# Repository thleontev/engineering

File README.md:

# Engineering

Репозиторий инженерных проектов и разработок.

Здесь собраны законченные и демонстрационные проекты по электронике, встроенному ПО, CAD, прототипированию и подготовке изделий к производству.

## Проекты

### Fire Lamp

Настольный ночник с эффектом пламени и светомузыкой на базе ESP32-S3 и WLED.

В проекте объединены:

- механическая конструкция и CAD;
- проектирование схемы и печатной платы;
- силовая часть для адресной LED-матрицы;
- встроенное ПО и пользовательский модуль WLED;
- датчик движения и датчик освещённости;
- сборка, прототипирование и испытания.

→ [Fire Lamp](fire-lamp/)

### Подсолнух / Sunflower

Настольный ночник в форме подсолнуха со сменной лампой GX53.

В проекте объединены:

- предметный дизайн и механическая компоновка;
- справочная сборка STEP;
- детали для FDM-печати и проект Bambu Studio;
- перечень компонентов и крепежа;
- вариант лампы YNDX-00556 с управлением через Алису;
- визуализация внешнего вида и внутреннего устройства.

→ [Подсолнух](sunflower/)

## Принцип публикации

В репозитории размещаются только материалы, которые подходят для публичного просмотра и воспроизведения проекта. Рабочие внутренние документы, данные поставщиков, учётные данные и незавершённые эксперименты не публикуются.

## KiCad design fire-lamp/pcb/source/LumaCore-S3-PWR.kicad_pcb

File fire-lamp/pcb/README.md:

# PCB — LumaCore-S3-PWR

Электроника Fire Lamp построена на контроллере LumaCore-S3-PWR.

## Рендеры платы

### Верхняя сторона

### Нижняя сторона

## Исходники

В каталоге `source/` находятся исходники KiCad:

- проект;
- принципиальная схема;
- печатная плата.

Используемые проектом символы, посадочные места и модели компонентов находятся в `source/lib/`. Таблицы `sym-lib-table` и `fp-lib-table` используют относительные пути. Для открытия проекта установите KiCad 10 со стандартными библиотеками и откройте `source/LumaCore-S3-PWR.kicad_pro`.

В каталоге `production/` размещены открытые производственные данные, которые можно использовать для анализа платы и подготовки сборки.

## Проверки опубликованного набора

Исходники, BOM, координаты и рендеры обновлены 4 ноября 2026 года. ERC и DRC выполнены повторно именно для опубликованной структуры каталогов в KiCad 10.0.8:

- ERC: 0 ошибок и предупреждений;
- DRC с перезаливкой зон и проверкой соответствия схеме: 0 нарушений, 0 неподключённых элементов, 0 расхождений;
- C4 и C14 указаны отдельными строками BOM; C14 100 мкФ присутствует в координатах установки.

Отчёты сохранены в `production/`. Эти проверки и подтверждение работы прототипа не являются квалификацией серийного производства, испытанием на 8 А или подтверждением тепловых пределов.

## Основные параметры

- MCU: ESP32-S3-WROOM-1;
- питание изделия: 5 В;
- нагрузка: WS2812B 16×16;
- LED DATA: отдельный буферизированный цифровой выход;
- управление питанием LED;
- отдельное питание логики 3,3 В.

## Ревизия

Опубликованный набор PCB основан на LumaCore-S3-PWR R2.1.

Плата является частью проекта Fire Lamp, но может использоваться и как самостоятельная аппаратная платформа.

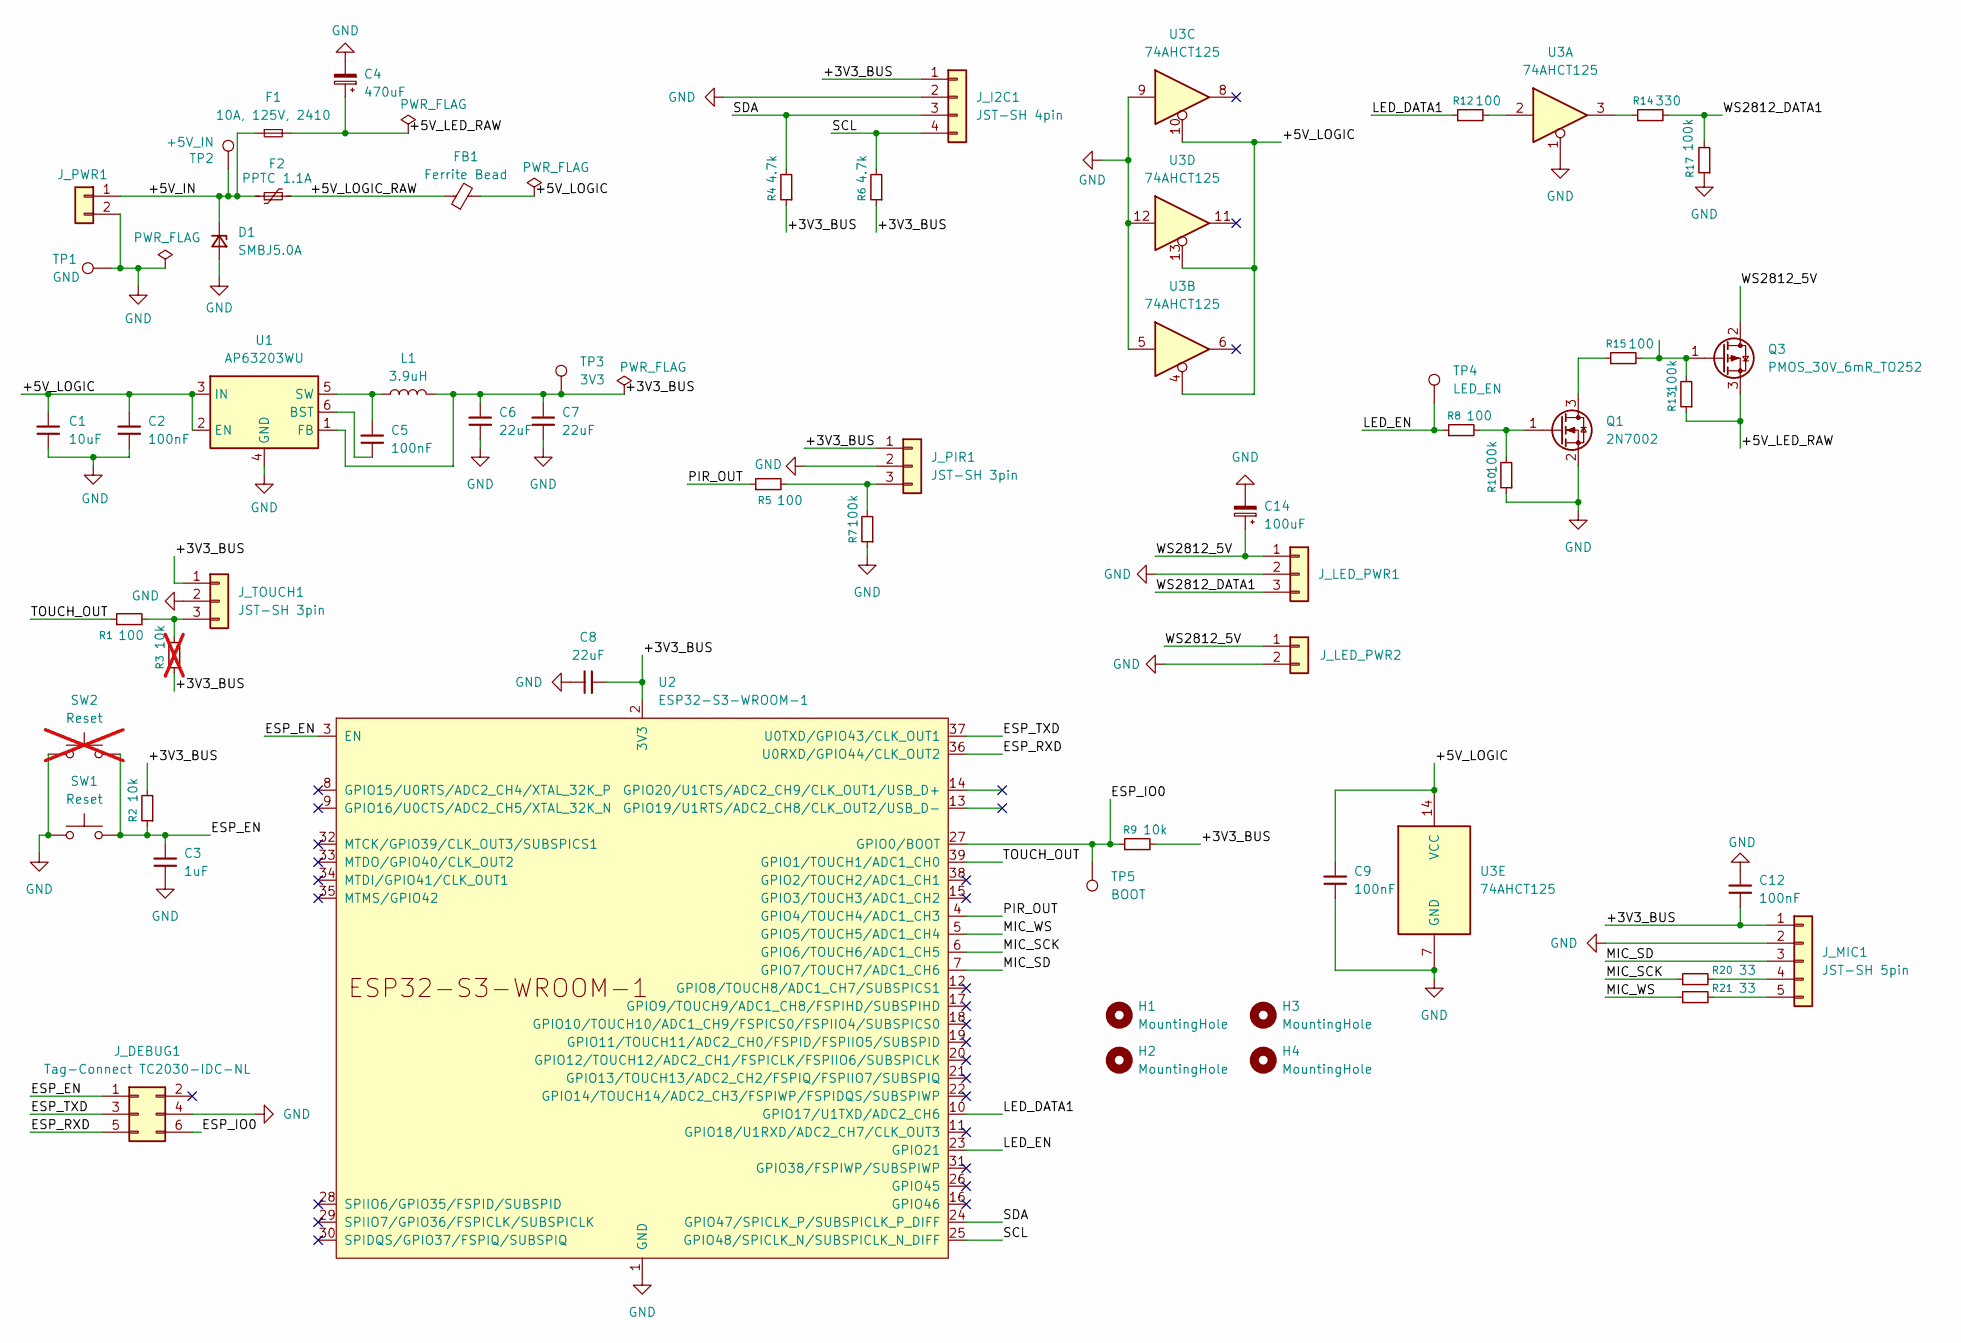
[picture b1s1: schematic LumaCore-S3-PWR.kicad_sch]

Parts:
C1: 10uF; C_1206_3216Metric
C2, C5, C9, C12: 100nF; C_0805_2012Metric
C3: 1uF; C_0805_2012Metric
C4: 470uF; CP_Elec_6.3x7.7; MPN EEEFTA471XAP
C6, C7, C8: 22uF; C_1206_3216Metric
C14: 100uF; CP_Elec_5x5.8; MPN EEE-FT1C101AR
D1: SMBJ5.0A; D_SMB; MPN SMBJ5.0A
F1: 10A, 125V, 2410; Fuse_Littelfuse_NANO2_452_2410; MPN 0451010.MRL
F2: PPTC 1.1A; Fuse_Polyfuse_Bourns_MF-MSMF110-16-2_1812; MPN MF-MSMF110/16-2
FB1: Ferrite Bead; L_0805_2012Metric; MPN BLM21PG121SN1D
H1, H2, H3, H4: MountingHole; MountingHole_2.2mm_M2
J_DEBUG1: Tag-Connect TC2030-IDC-NL; Tag-Connect_TC2030-IDC-NL_2x03_P1.27mm_Vertical
J_I2C1: JST-SH 4pin; JST_SH_BM04B-SRSS-TB_1x04-1MP_P1.00mm_Vertical
J_LED_PWR1: SolderCable_1x03_AWG16_DATA_P4.50_D2.00
J_LED_PWR2: SolderCable_1x02_AWG16_P4.50_D2.00
J_MIC1: JST-SH 5pin; JST_SH_BM05B-SRSS-TB_1x05-1MP_P1.00mm_Vertical
J_PIR1: JST-SH 3pin; JST_SH_BM03B-SRSS-TB_1x03-1MP_P1.00mm_Vertical
J_PWR1: SolderCable_1x02_AWG16_P4.50_D2.00
J_TOUCH1: JST-SH 3pin; JST_SH_BM03B-SRSS-TB_1x03-1MP_P1.00mm_Vertical
L1: 3.9uH; L_4020_4030_Universal_LumaCore; MPN MNR4030T3R9MT
Q1: 2N7002; SOT-23; MPN 2N7002
Q3: PMOS_30V_6mR_TO252; TO-252-3_TabPin2; MPN G050P03K
R1, R5, R8, R12, R15: 100; R_0805_2012Metric
R2, R9: 10k; R_0805_2012Metric
R3: 10k; R_0805_2012Metric; not fitted
R4, R6: 4.7k; R_0805_2012Metric
R7, R10, R13, R17: 100k; R_0805_2012Metric
R14: 330; R_0805_2012Metric
R20, R21: 33; R_0805_2012Metric
SW1: Reset; SW_SPST_B3U-1000P; MPN B3U-1000P
SW2: Reset; SW_SPST_B3U-1000P; MPN B3U-1000P; not fitted
TP1: GND; TestPoint_Pad_D1.0mm
TP2: +5V_IN; TestPoint_Pad_D1.0mm
TP3: 3V3; TestPoint_Pad_D1.0mm
TP4: LED_EN; TestPoint_Pad_D1.0mm
TP5: BOOT; TestPoint_Pad_D1.0mm
U1: AP63203WU; TSOT-23-6; MPN AP63203WU-7
U2: ESP32-S3-WROOM-1; MPN ESP32-S3-WROOM-1(16R8)
U3: 74AHCT125; SOIC-14_3.9x8.7mm_P1.27mm; MPN SN74AHCT125DR

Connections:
/+3V3_BUS: C6.1, C7.1, C8.1, C12.2, J_I2C1.1, J_MIC1.1, J_PIR1.1, J_TOUCH1.1, L1.2, R2.2, R3.1, R4.1, R6.1, R9.2, TP3.1 (1_1), U1.1 (FB), U2.2 (3V3)
/+5V_IN: D1.1 (K), F1.1, F2.1, J_PWR1.1, TP2.1 (1_1)
/+5V_LED_RAW: C4.1, F1.2, Q3.3 (S), R13.1
/+5V_LOGIC: C1.1, C2.1, C9.1, FB1.2, U1.2 (EN), U1.3 (IN), U3.4, U3.10, U3.13, U3.14 (VCC)
/+5V_LOGIC_RAW: F2.2, FB1.1
/ESP_EN: C3.1, J_DEBUG1.1, R2.1, SW1.2, SW2.2, U2.3 (EN)
/ESP_IO0: J_DEBUG1.6, R9.1, TP5.1 (1_1), U2.27 (GPIO0/BOOT)
/ESP_RXD: J_DEBUG1.5, U2.36 (U0RXD/GPIO44/CLK_OUT2)
/ESP_TXD: J_DEBUG1.3, U2.37 (U0TXD/GPIO43/CLK_OUT1)
/LED_DATA1: R12.1, U2.10 (GPIO17/U1TXD/ADC2_CH6)
/LED_EN: R8.1, TP4.1 (1_1), U2.23 (GPIO21)
/MIC_SCK: R20.1, U2.6 (GPIO6/TOUCH6/ADC1_CH5)
/MIC_SD: J_MIC1.3, U2.7 (GPIO7/TOUCH7/ADC1_CH6)
/MIC_WS: R21.1, U2.5 (GPIO5/TOUCH5/ADC1_CH4)
/PIR_OUT: R5.1, U2.4 (GPIO4/TOUCH4/ADC1_CH3)
/SCL: J_I2C1.4, R6.2, U2.25 (GPIO48/SPICLK_N/SUBSPICLK_N_DIFF)
/SDA: J_I2C1.3, R4.2, U2.24 (GPIO47/SPICLK_P/SUBSPICLK_P_DIFF)
/TOUCH_OUT: R1.1, U2.39 (GPIO1/TOUCH1/ADC1_CH0)
/WS2812_5V: C14.1, J_LED_PWR1.1, J_LED_PWR2.1, Q3.2 (D)
/WS2812_DATA1: J_LED_PWR1.3, R14.2, R17.2
GND: C1.2, C2.2, C3.2, C4.2, C6.2, C7.2, C8.2, C9.2, C12.1, C14.2, D1.2 (A), J_DEBUG1.4, J_I2C1.2, J_LED_PWR1.2, J_LED_PWR2.2, J_MIC1.2, J_PIR1.2, J_PWR1.2, J_TOUCH1.2, Q1.2 (S), R7.1, R10.1, R17.1, SW1.1, SW2.1, TP1.1 (1_1), U1.4 (GND), U2.1 (GND), U2.40 (GND), U2.41 (GND), U3.1, U3.5, U3.7 (GND), U3.9, U3.12
unnamed: J_MIC1.4, R20.2
unnamed: J_MIC1.5, R21.2
unnamed: J_PIR1.3, R5.2, R7.2
unnamed: J_TOUCH1.3, R1.2, R3.2
unnamed: Q1.3 (D), R15.1
unnamed: Q1.1 (G), R8.2, R10.2
unnamed: Q3.1 (G), R13.2, R15.2
unnamed: R12.2, U3.2
unnamed: R14.1, U3.3
unnamed: C5.2, U1.6 (BST)
unnamed: C5.1, L1.1, U1.5 (SW)

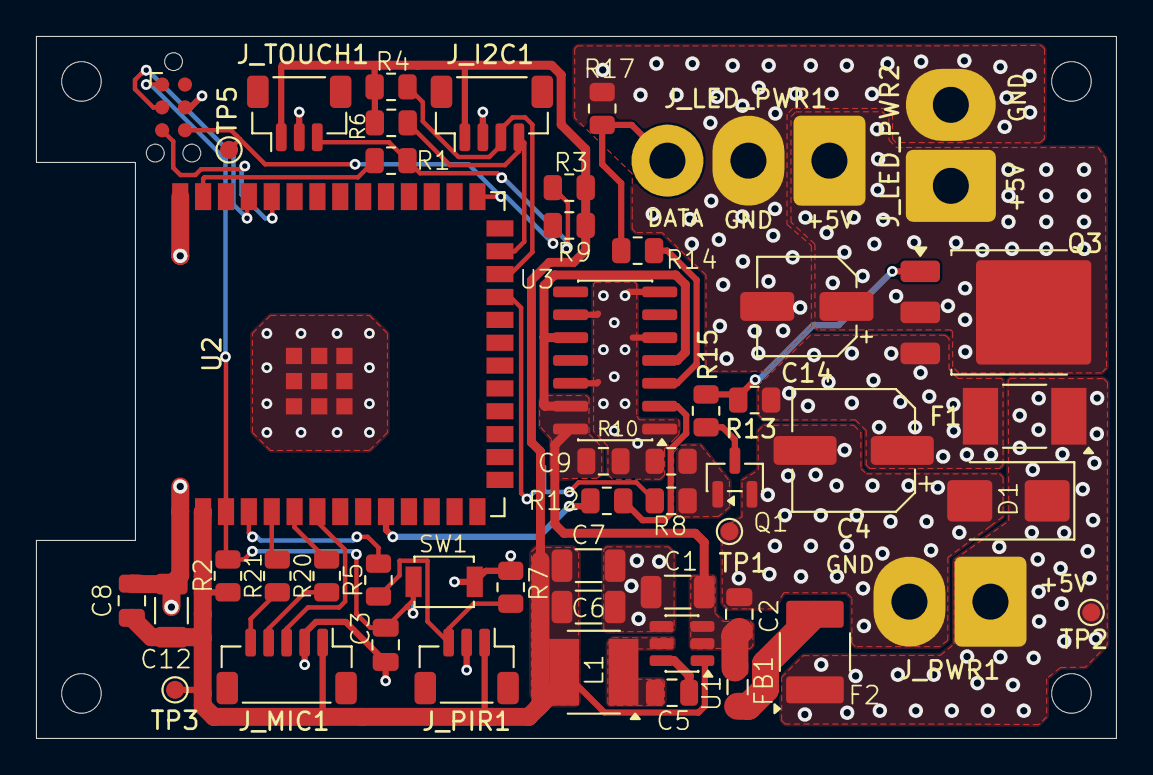
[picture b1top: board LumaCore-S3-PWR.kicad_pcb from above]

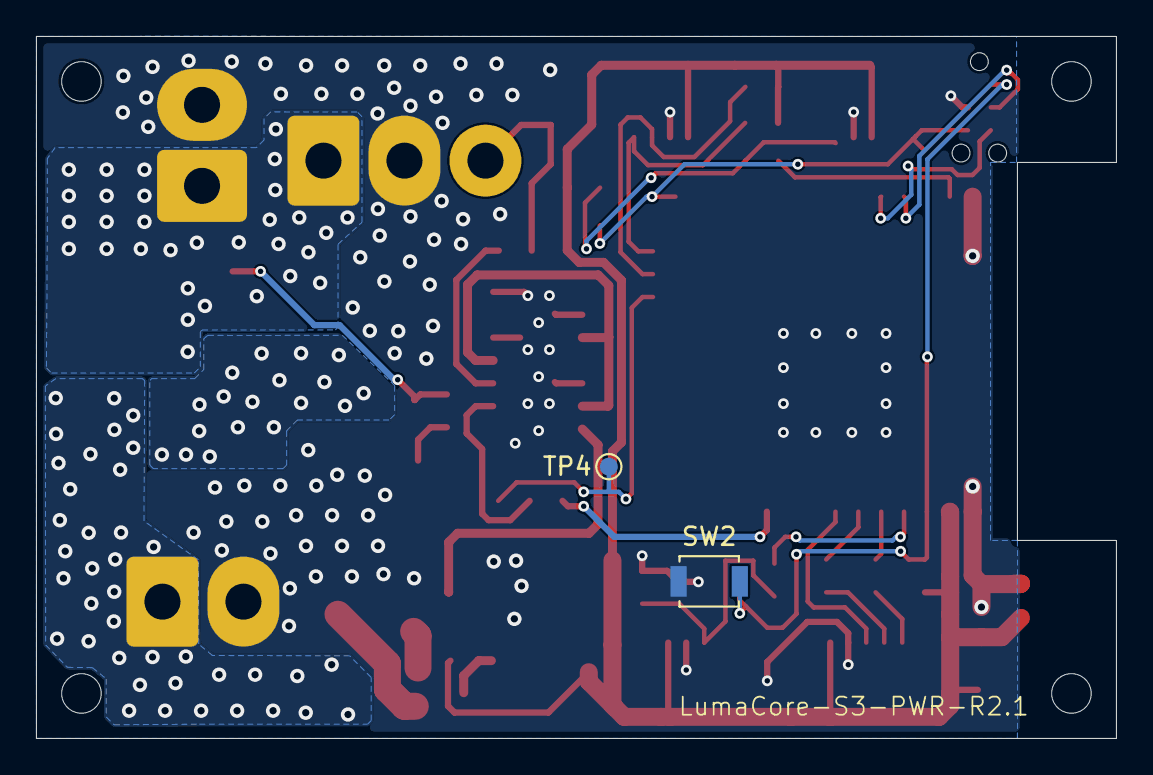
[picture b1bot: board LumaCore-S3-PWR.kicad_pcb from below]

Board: 2 copper layers, 60.0 x 39.0 mm, 57 parts (2 on the bottom side), 32 nets.

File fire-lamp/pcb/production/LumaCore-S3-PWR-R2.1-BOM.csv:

"Refs","Qty","Value","Footprint","Manufacturer","MPN","Supplier","Description","Specification"
"C1","1","10uF","Capacitor_SMD:C_1206_3216Metric","","","","Unpolarized capacitor, small symbol","10uF; 10V; X5R; ±10%; 1206"
"C2, C5, C9, C12","4","100nF","Capacitor_SMD:C_0805_2012Metric","","","","Unpolarized capacitor, small symbol","100nF; 50V; X7R; ±10%; 0805"
"C3","1","1uF","Capacitor_SMD:C_0805_2012Metric","","","","Unpolarized capacitor, small symbol","1uF; 16V; X7R; ±10%; 0805"
"C4","1","470uF","Capacitor_SMD:CP_Elec_6.3x7.7","","EEEFTA471XAP","","470uF 10V 105C SMD D6.3x7.7","470uF; 10V; 105°C; SMD 6.3x7.7mm"
"C6-C8","3","22uF","Capacitor_SMD:C_1206_3216Metric","","","","Unpolarized capacitor, small symbol","22uF; 10V; X7R; ±10%; 1206"
"C14","1","100uF","Capacitor_SMD:CP_Elec_5x5.8","","EEE-FT1C101AR","","100uF 16V 105C SMD 5x5.8","100uF; 16V; 105°C; SMD 5x5.8mm"
"D1","1","SMBJ5.0A","Diode_SMD:D_SMB","","SMBJ5.0A","","Unidirectional TVS diode, 600W, 5V, SMB / DO-214AA","TVS; SMBJ5.0A; 5.0V; 600W; SMB (DO-214AA)"
"F1","1","10A, 125V, 2410","LumaCore:Fuse_Littelfuse_NANO2_452_2410","","0451010.MRL","","10A, 125V, 2410","Fuse; 10A; 125V; 2410"
"F2","1","PPTC 1.1A","LumaCore:Fuse_Polyfuse_Bourns_MF-MSMF110-16-2_1812","","MF-MSMF110/16-2","","PPTC resettable fuse, 1.1A hold, 2.2A trip, 16V, 1812","PPTC; Ihold 1.1A; Vmax 16V; 1812"
"FB1","1","Ferrite Bead","Inductor_SMD:L_0805_2012Metric","","BLM21PG121SN1D","","Ferrite bead, 120Ω @100MHz, 3A, 30mΩ max, 0805/2012, Murata BLM21PG series","Ferrite bead; 120Ω @100MHz; 3A; 0805"
"J_I2C1","1","JST-SH 4pin","Connector_JST:JST_SH_BM04B-SRSS-TB_1x04-1MP_P1.00mm_Vertical","","","","Generic connector, single row, 01x04, script generated (kicad-library-utils/schlib/autogen/connector/)","JST SH; 4 pin; 1.0mm; vertical SMD"
"J_MIC1","1","JST-SH 5pin","Connector_JST:JST_SH_BM05B-SRSS-TB_1x05-1MP_P1.00mm_Vertical","","","","Generic connector, single row, 01x05, script generated (kicad-library-utils/schlib/autogen/connector/)","JST SH; 5 pin; 1.0mm; vertical SMD"
"J_PIR1, J_TOUCH1","2","JST-SH 3pin","Connector_JST:JST_SH_BM03B-SRSS-TB_1x03-1MP_P1.00mm_Vertical","","","","Generic connector, single row, 01x03, script generated (kicad-library-utils/schlib/autogen/connector/)","JST SH; 3 pin; 1.0mm; vertical SMD"
"L1","1","3.9uH","LumaCore:L_4020_4030_Universal_LumaCore","","MNR4030T3R9MT","","Inductor","Inductor; 3.9uH; ±20%; current rating ≥3.3A; SMD 4x4mm"
"Q1","1","2N7002","Package_TO_SOT_SMD:SOT-23","","2N7002","","N-channel MOSFET, 60V, 115mA, SOT-23-3","N-MOSFET; VDS ≥60V; ID ≥115mA; SOT-23-3"
"Q3","1","PMOS_30V_6mR_TO252","Package_TO_SOT_SMD:TO-252-3_TabPin2","","G050P03K","","P-MOSFET, -30 V, RDS(on) ≤6 mΩ @ VGS=-4.5 V, TO-252, 1G-2D-3S","P-MOSFET; VDS -30V; RDS(on) ≤6mΩ @ VGS -4.5V; TO-252; 1G-2D-3S"
"R1, R5, R8, R12, R15","5","100","Resistor_SMD:R_0805_2012Metric","","","","Resistor, small symbol","100Ω; ±1%; 0.125W; 0805; thick-film"
"R2, R9","2","10k","Resistor_SMD:R_0805_2012Metric","","","","Resistor, small symbol","10kΩ; ±1%; 0.125W; 0805; thick-film"
"R4, R6","2","4.7k","Resistor_SMD:R_0805_2012Metric","","","","Resistor, small symbol","4.7kΩ; ±1%; 0.125W; 0805; thick-film"
"R7, R10, R13, R17","4","100k","Resistor_SMD:R_0805_2012Metric","","","","Resistor, small symbol","100kΩ; ±1%; 0.125W; 0805; thick-film"
"R14","1","330","Resistor_SMD:R_0805_2012Metric","","","","Resistor, small symbol","330Ω; ±1%; 0.125W; 0805; thick-film"
"R20, R21","2","33","Resistor_SMD:R_0805_2012Metric","","","","Resistor, small symbol","33Ω; ±1%; 0.125W; 0805; thick-film"
"SW1","1","Reset","Button_Switch_SMD:SW_SPST_B3U-1000P","","B3U-1000P","","Push button switch, generic, two pins","Tactile switch; SPST; B3U-1000P; SMD"
"U1","1","AP63203WU","Package_TO_SOT_SMD:TSOT-23-6","","AP63203WU-7","","2A, 1.1MHz Buck DC/DC Converter, fixed 3.3V output voltage, TSOT-23-6","Buck DC/DC; 3.3V output; 2A; 1.1MHz; TSOT-23-6"
"U2","1","ESP32-S3-WROOM-1","LumaCore:ESP32-S3-WROOM-1","","ESP32-S3-WROOM-1(16R8)","","2.4 GHz WiFi (802.11 b/g/n) and Bluetooth ® 5 (LE) module Built around ESP32S3 series of SoCs, Xtensa ® dualcore 32bit LX7 microprocessor Flash up to 16 MB, PSRAM up to 8 MB 36 GPIOs, rich set of peripherals Onboard PCB antenna","ESP32-S3-WROOM-1(16R8); Wi-Fi/BLE; PCB antenna"
"U3","1","74AHCT125","Package_SO:SOIC-14_3.9x8.7mm_P1.27mm","","SN74AHCT125DR","","Quadruple Bus Buffer Gates With 3-State Outputs","74AHCT125; 5V logic buffer; SOIC-14"
